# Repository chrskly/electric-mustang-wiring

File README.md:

# Electric Mustang Wiring

This repo contains the circuits, software, and wiring diagrams for my project to
convert a 1965 Ford Mustang to a EV.

## bms - Battery Management System

Schematic, PCB, and software for the battery management system.

## 12v-front-pcb

Schematic and PCB for wiring that sits in the front of the car (engine bay).

* Ignition switch
* Drive inhibition (preventing driving off when charging)
* Coolant pump
* Inverter
* Contactors
* Shunt

## 12v-lighting

Schematic and PCB for wiring for all of the lighting.

* Headlights/highbeams
* Indicators
* Brake lights
* Interior lights

## 12v-rear-pcb

Schematic and PCB for wiring that sits in the rear of the car (boot).

* On-board AC charger
* DC charger
* Charger VCU

## dashboard-vcu

Schematic and PCB for VCU to control the car dashboard.

## dashboard-vcu-src

Source code of dashboard vcu firmware.

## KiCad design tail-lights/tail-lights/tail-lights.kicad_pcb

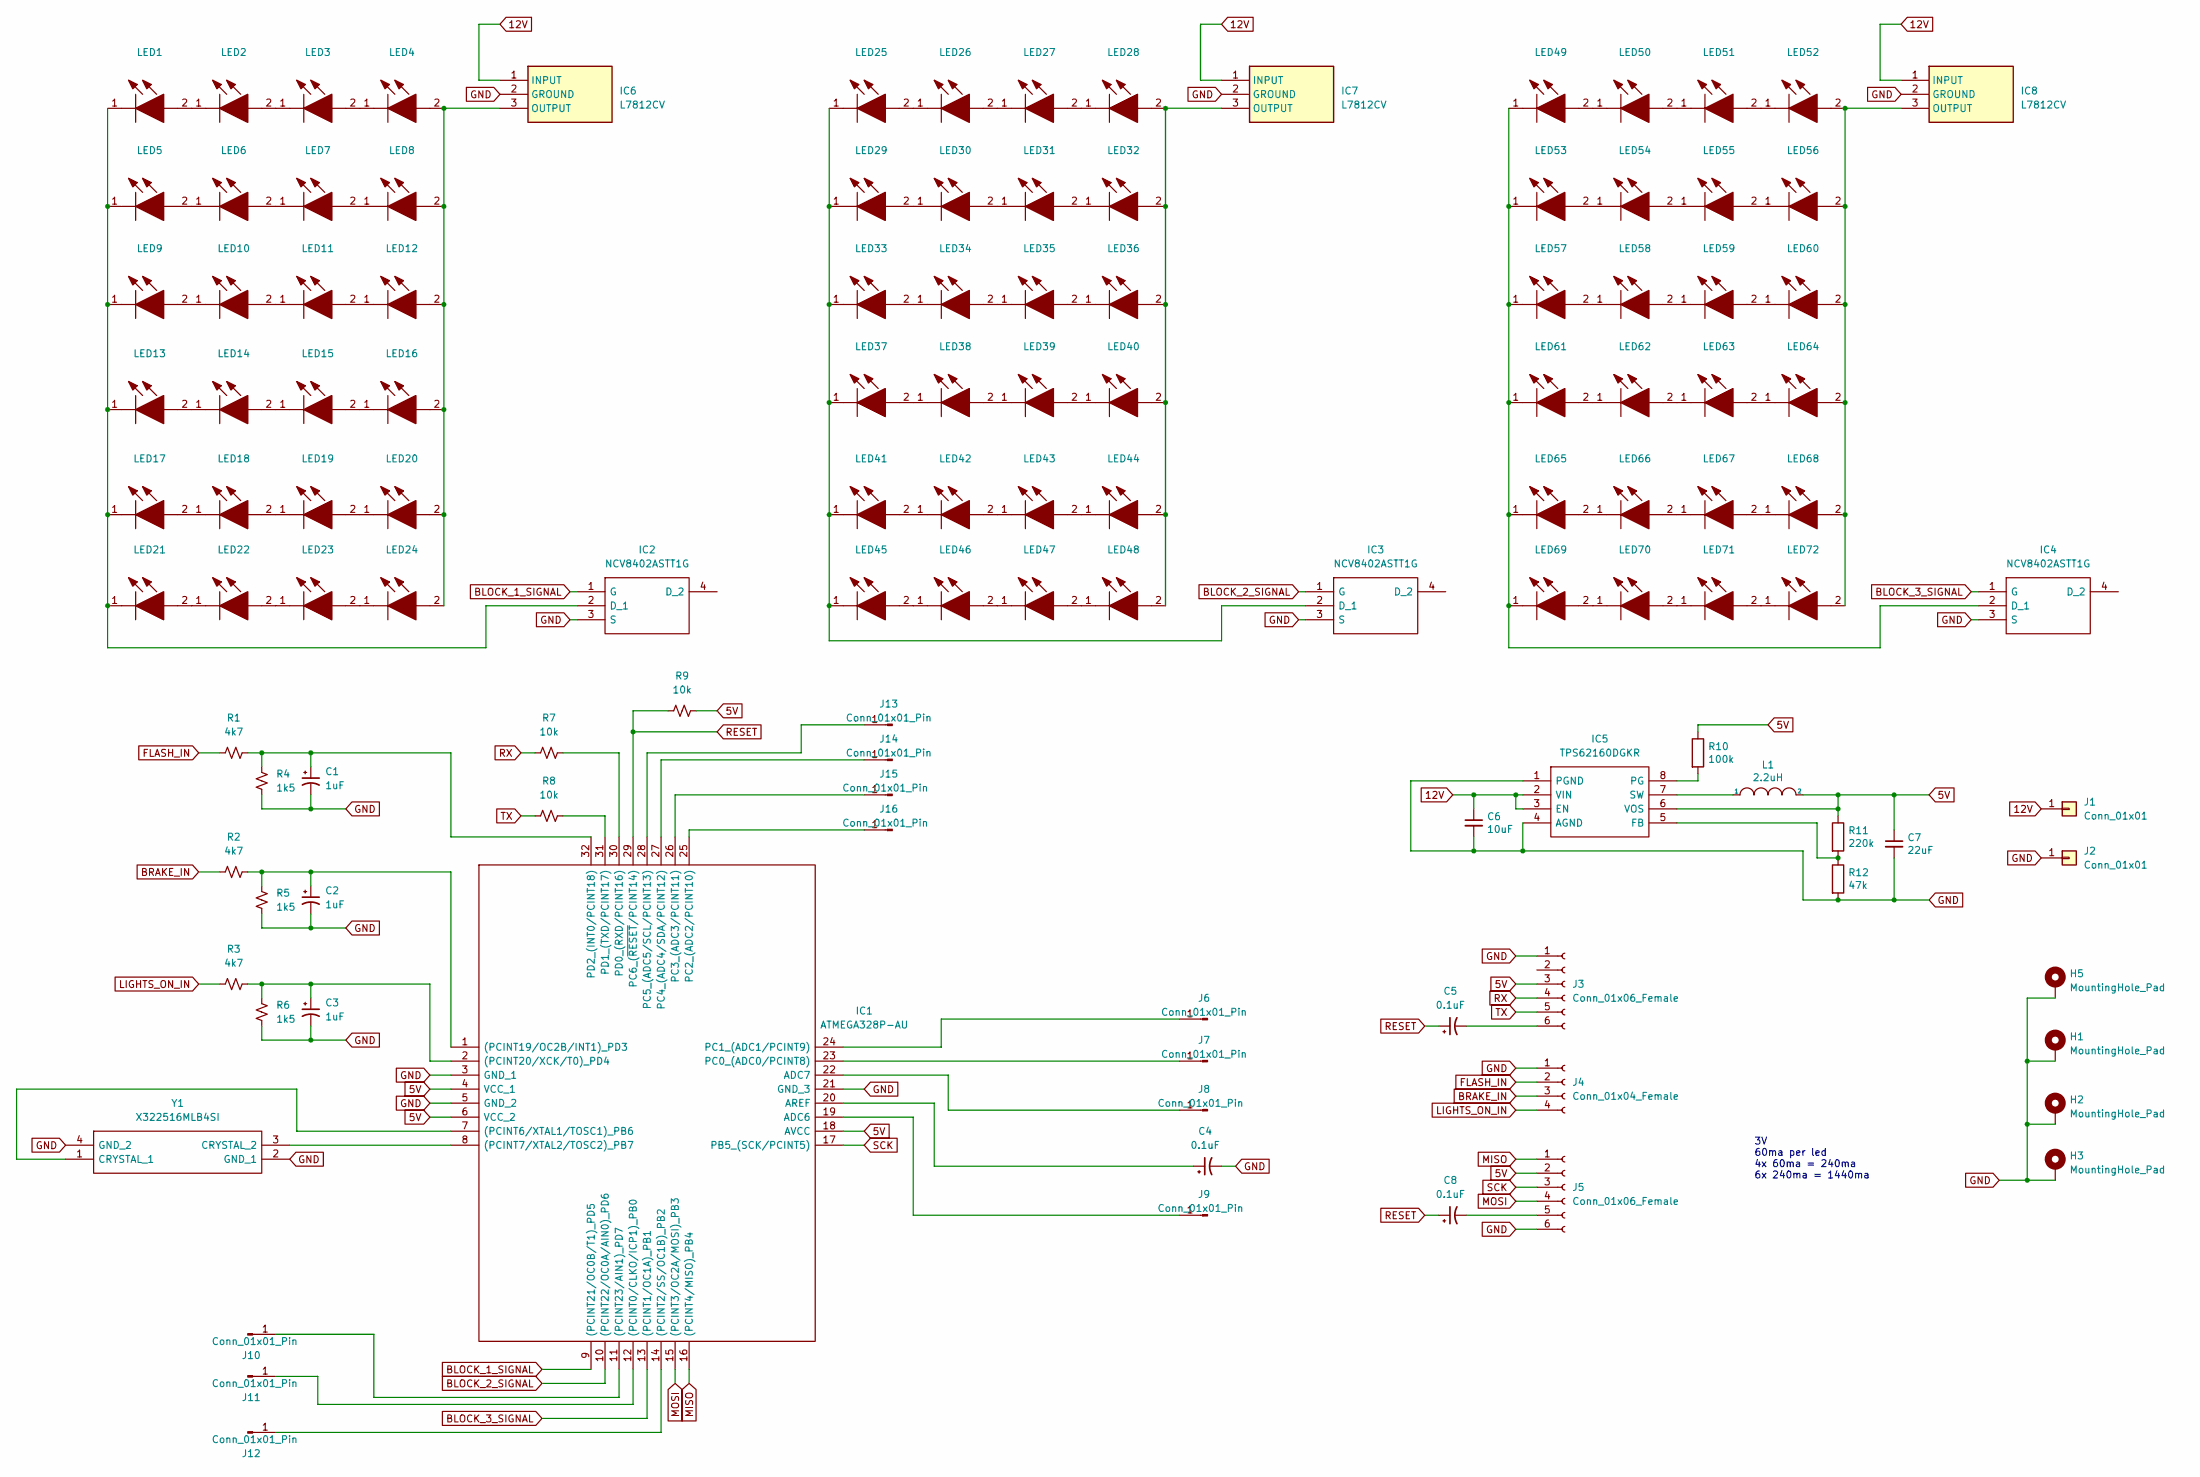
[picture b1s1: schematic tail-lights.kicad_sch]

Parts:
C1, C2, C3: 1uF; C_0603_1608Metric
C4, C5, C8: 0.1uF; C_0603_1608Metric
C6: 10uF; C_0603_1608Metric
C7: 22uF; C_0805_2012Metric
H1, H2, H3, H5: MountingHole_Pad; MountingHole_2.5mm_Pad
IC1: ATMEGA328P-AU; QFP80P900X900X120-32N; Manufacturer_Part_Number ATMEGA328P-AU; Mouser Part Number 556-ATMEGA328P-AU
IC2, IC3, IC4: NCV8402ASTT1G; SOT230P700X175-4N; Manufacturer_Part_Number NCV8402ASTT1G; Mouser Part Number 863-NCV8402ASTT1G
IC5: TPS62160DGKR; SOP65P490X110-8N; Manufacturer_Part_Number TPS62160DGKR; Mouser Part Number 595-TPS62160DGKR
IC6, IC7, IC8: L7812CV; TO255P460X1020X2008-3P; Manufacturer_Part_Number L7812CV; Mouser Part Number 511-L7812CV
J1, J2: Conn_01x01; SolderWire-1sqmm_1x01_D1.4mm_OD2.7mm
J3, J5: Conn_01x06_Female; PinHeader_1x06_P2.54mm_Vertical
J4: Conn_01x04_Female; PinHeader_1x04_P2.54mm_Vertical
J6, J7, J8, J9, J10, J11, J12, J13, J14, J15, J16: Conn_01x01_Pin; PinHeader_1x01_P2.54mm_Vertical
L1: 2.2uH; NR6028T220M
LED1, LED2, LED3, LED4, LED5, LED6, LED7, LED8, LED9, LED10, LED11, LED12, LED13, LED14, LED15, LED16, LED17, LED18, LED19, LED20, LED21, LED22, LED23, LED24, LED25, LED26, LED27, LED28, LED29, LED30, LED31, LED32, LED33, LED34, LED35, LED36, LED37, LED38, LED39, LED40, LED41, LED42, LED43, LED44, LED45, LED46, LED47, LED48, LED49, LED50, LED51, LED52, LED53, LED54, LED55, LED56, LED57, LED58, LED59, LED60, LED61, LED62, LED63, LED64, LED65, LED66, LED67, LED68, LED69, LED70, LED71, LED72: HL-AM-2835H421W-S1-08-HR3; HLAM2835H421WS108HR3; Manufacturer_Part_Number HL-AM-2835H421W-S1-08-HR3
R1, R2, R3: 4k7; R_0805_2012Metric
R4, R5, R6: 1k5; R_0805_2012Metric
R7, R8, R9: 10k; R_0805_2012Metric
R10: 100k; R_0805_2012Metric
R11: 220k; R_0805_2012Metric
R12: 47k; R_0805_2012Metric
Y1: X322516MLB4SI; Manufacturer_Part_Number X322516MLB4SI

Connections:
5V: C7.1, IC1.4 (VCC_1), IC1.6 (VCC_2), IC1.18 (AVCC), IC5.6 (VOS), J3.3, J5.2, L1.2, R9.2, R10.1, R11.1
12V: C6.1, IC5.2 (VIN), IC5.3 (EN), IC6.1 (INPUT), IC7.1 (INPUT), IC8.1 (INPUT), J1.1
BLOCK_1_SIGNAL: IC1.9 ((PCINT21/OC0B/T1)_PD5), IC2.1 (G)
BLOCK_2_SIGNAL: IC1.10 ((PCINT22/OC0A/AIN0)_PD6), IC3.1 (G)
BLOCK_3_SIGNAL: IC1.13 ((PCINT1/OC1A)_PB1), IC4.1 (G)
BRAKE_IN: J4.3, R2.1
FLASH_IN: J4.2, R1.1
GND: C1.2, C2.2, C3.2, C4.2, C6.2, C7.2, H1.1, H2.1, H3.1, H5.1, IC1.3 (GND_1), IC1.5 (GND_2), IC1.21 (GND_3), IC2.3 (S), IC3.3 (S), IC4.3 (S), IC5.1 (PGND), IC5.4 (AGND), IC6.2 (GROUND), IC7.2 (GROUND), IC8.2 (GROUND), J2.1, J3.1, J4.1, J5.6, R4.2, R5.2, R6.2, R12.2, Y1.2 (GND_1), Y1.4 (GND_2)
LIGHTS_ON_IN: J4.4, R3.1
MISO: IC1.16 ((PCINT4/MISO)_PB4), J5.1
MOSI: IC1.15 ((PCINT3/OC2A/MOSI)_PB3), J5.4
unnamed: IC1.12 ((PCINT0/CLKO/ICP1)_PB0), J11.1
unnamed: IC1.14 ((PCINT2/SS/OC1B)_PB2), J12.1
unnamed: IC1.7 ((PCINT6/XTAL1/TOSC1)_PB6), Y1.1 (CRYSTAL_1)
unnamed: IC1.8 ((PCINT7/XTAL2/TOSC2)_PB7), Y1.3 (CRYSTAL_2)
unnamed: C2.1, IC1.1 ((PCINT19/OC2B/INT1)_PD3), R2.2, R5.1
unnamed: C3.1, IC1.2 ((PCINT20/XCK/T0)_PD4), R3.2, R6.1
unnamed: IC1.11 ((PCINT23/AIN1)_PD7), J10.1
unnamed: IC1.19 (ADC6), J9.1
unnamed: IC1.22 (ADC7), J8.1
unnamed: C4.1, IC1.20 (AREF)
unnamed: IC1.23 (PC0_(ADC0/PCINT8)), J7.1
unnamed: IC1.24 (PC1_(ADC1/PCINT9)), J6.1
unnamed: IC1.25 (PC2_(ADC2/PCINT10)), J16.1
unnamed: IC1.26 (PC3_(ADC3/PCINT11)), J15.1
unnamed: IC1.27 (PC4_(ADC4/SDA/PCINT12)), J14.1
unnamed: IC1.28 (PC5_(ADC5/SCL/PCINT13)), J13.1
unnamed: IC1.30 (PD0_(RXD/PCINT16)), R7.2
unnamed: IC1.31 (PD1_(TXD/PCINT17)), R8.2
unnamed: C1.1, IC1.32 (PD2_(INT0/PCINT18)), R1.2, R4.1
unnamed: IC2.2 (D_1), LED1.1, LED5.1, LED9.1, LED13.1, LED17.1, LED21.1
unnamed: IC3.2 (D_1), LED25.1, LED29.1, LED33.1, LED37.1, LED41.1, LED45.1
unnamed: IC4.2 (D_1), LED49.1, LED53.1, LED57.1, LED61.1, LED65.1, LED69.1
unnamed: IC5.5 (FB), R11.2, R12.1
unnamed: IC5.8 (PG), R10.2
unnamed: IC5.7 (SW), L1.1
unnamed: IC6.3 (OUTPUT), LED4.2, LED8.2, LED12.2, LED16.2, LED20.2, LED24.2
unnamed: IC7.3 (OUTPUT), LED28.2, LED32.2, LED36.2, LED40.2, LED44.2, LED48.2
unnamed: IC8.3 (OUTPUT), LED52.2, LED56.2, LED60.2, LED64.2, LED68.2, LED72.2
unnamed: C5.2, J3.6
unnamed: C8.2, J5.5
unnamed: LED1.2, LED2.1
unnamed: LED2.2, LED3.1
unnamed: LED3.2, LED4.1
unnamed: LED5.2, LED6.1
unnamed: LED6.2, LED7.1
unnamed: LED7.2, LED8.1
unnamed: LED9.2, LED10.1
unnamed: LED10.2, LED11.1
unnamed: LED11.2, LED12.1
unnamed: LED13.2, LED14.1
unnamed: LED14.2, LED15.1
unnamed: LED15.2, LED16.1
unnamed: LED17.2, LED18.1
unnamed: LED18.2, LED19.1
unnamed: LED19.2, LED20.1
unnamed: LED21.2, LED22.1
unnamed: LED22.2, LED23.1
unnamed: LED23.2, LED24.1
unnamed: LED25.2, LED26.1
unnamed: LED26.2, LED27.1
unnamed: LED27.2, LED28.1
unnamed: LED29.2, LED30.1
unnamed: LED30.2, LED31.1
unnamed: LED31.2, LED32.1
unnamed: LED33.2, LED34.1
unnamed: LED34.2, LED35.1
unnamed: LED35.2, LED36.1
unnamed: LED37.2, LED38.1
unnamed: LED38.2, LED39.1
unnamed: LED39.2, LED40.1
unnamed: LED41.2, LED42.1
unnamed: LED42.2, LED43.1
unnamed: LED43.2, LED44.1
unnamed: LED45.2, LED46.1
unnamed: LED46.2, LED47.1
unnamed: LED47.2, LED48.1
unnamed: LED49.2, LED50.1
unnamed: LED50.2, LED51.1
unnamed: LED51.2, LED52.1
unnamed: LED53.2, LED54.1
unnamed: LED54.2, LED55.1
unnamed: LED55.2, LED56.1
unnamed: LED57.2, LED58.1
unnamed: LED58.2, LED59.1
unnamed: LED59.2, LED60.1
unnamed: LED61.2, LED62.1
unnamed: LED62.2, LED63.1
unnamed: LED63.2, LED64.1
unnamed: LED65.2, LED66.1
unnamed: LED66.2, LED67.1
unnamed: LED67.2, LED68.1
unnamed: LED69.2, LED70.1
unnamed: LED70.2, LED71.1
unnamed: LED71.2, LED72.1
RESET: C5.1, C8.1, IC1.29 (PC6_(~RESET/PCINT14)), R9.1
RX: J3.4, R7.1
SCK: IC1.17 (PB5_(SCK/PCINT5)), J5.3
TX: J3.5, R8.1

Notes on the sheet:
3V 60ma per led 4x 60ma = 240ma 6x 240ma = 1440ma

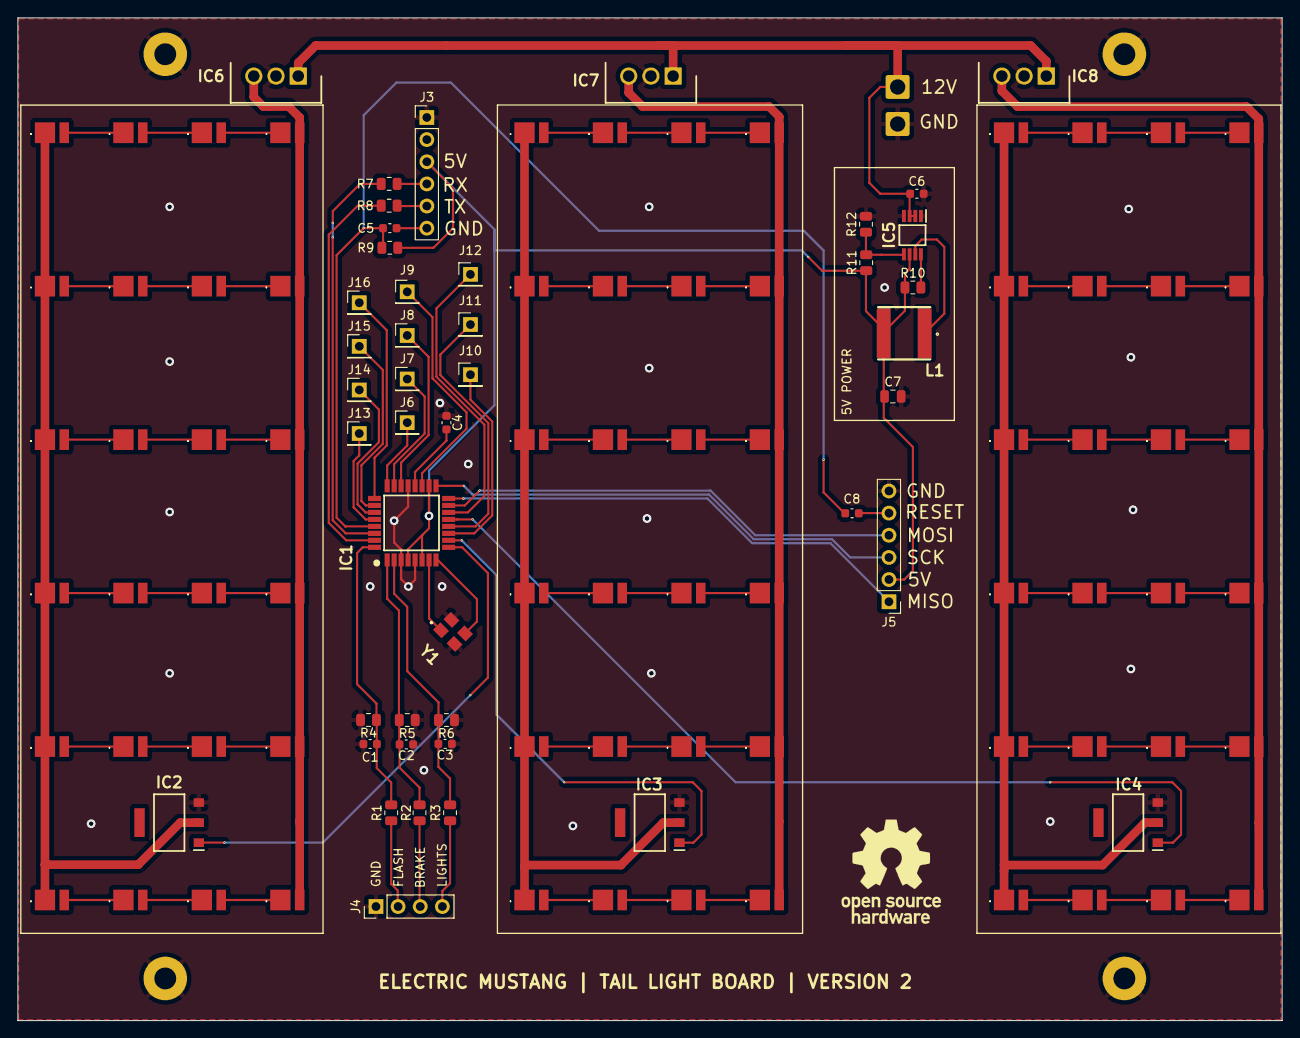
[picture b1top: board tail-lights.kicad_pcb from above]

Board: 2 copper layers, 145.0 x 115.0 mm, 122 parts (0 on the bottom side), 99 nets.

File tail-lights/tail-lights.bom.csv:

Comment,Designator,Footprint,LCSC
HL-AM-2835H421W-S1-08-HR3,"LED1,LED2,LED3,LED4,LED5,LED6,LED7,LED8,LED9,LED10,LED11,LED12,LED13,LED14,LED15,LED16,LED17,LED18,LED19,LED20,LED21,LED22,LED23,LED24,LED25,LED26,LED27,LED28,LED29,LED30,LED31,LED32,LED33,LED34,LED35,LED36,LED37,LED38,LED39,LED40,LED41,LED42,LED43,LED44,LED45,LED46,LED47,LED48,LED49,LED50,LED51,LED52,LED53,LED54,LED55,LED56,LED57,LED58,LED59,LED60,LED61,LED62,LED63,LED64,LED65,LED66,LED67,LED68,LED69,LED70,LED71,LED72",SMD2835,C210318
NCV8402ASTT1G,"IC2,IC3,IC4",SOT223,C77755
ATMEGA328P-AU,IC1,TQFP-32,C14877
4k7Ω,"R1,R2,R3",0805_R,C17673
1k5Ω,"R4,R5,R6",0805_R,C4310
1uF,"C1,C2,C3",0805_C,C28323
X322516MLB4SI,Y1,SMD3225-4P,C13738
10kΩ,"R7,R8,R9",0805_R,C84376
0.1uF,"C4,C5",0805_C,C49678
TPS62160DGKR,IC5,MSOP-8,C60726
10uF,C6,0805_C,C15850
100kΩ,R10,0805_R,C149504
2.2uH,L1,SMD,C135262
220kΩ,R11,0805_R,C17539
47kΩ,R12,0805_R,C17713
22uF,C7,0805_C,C2835558

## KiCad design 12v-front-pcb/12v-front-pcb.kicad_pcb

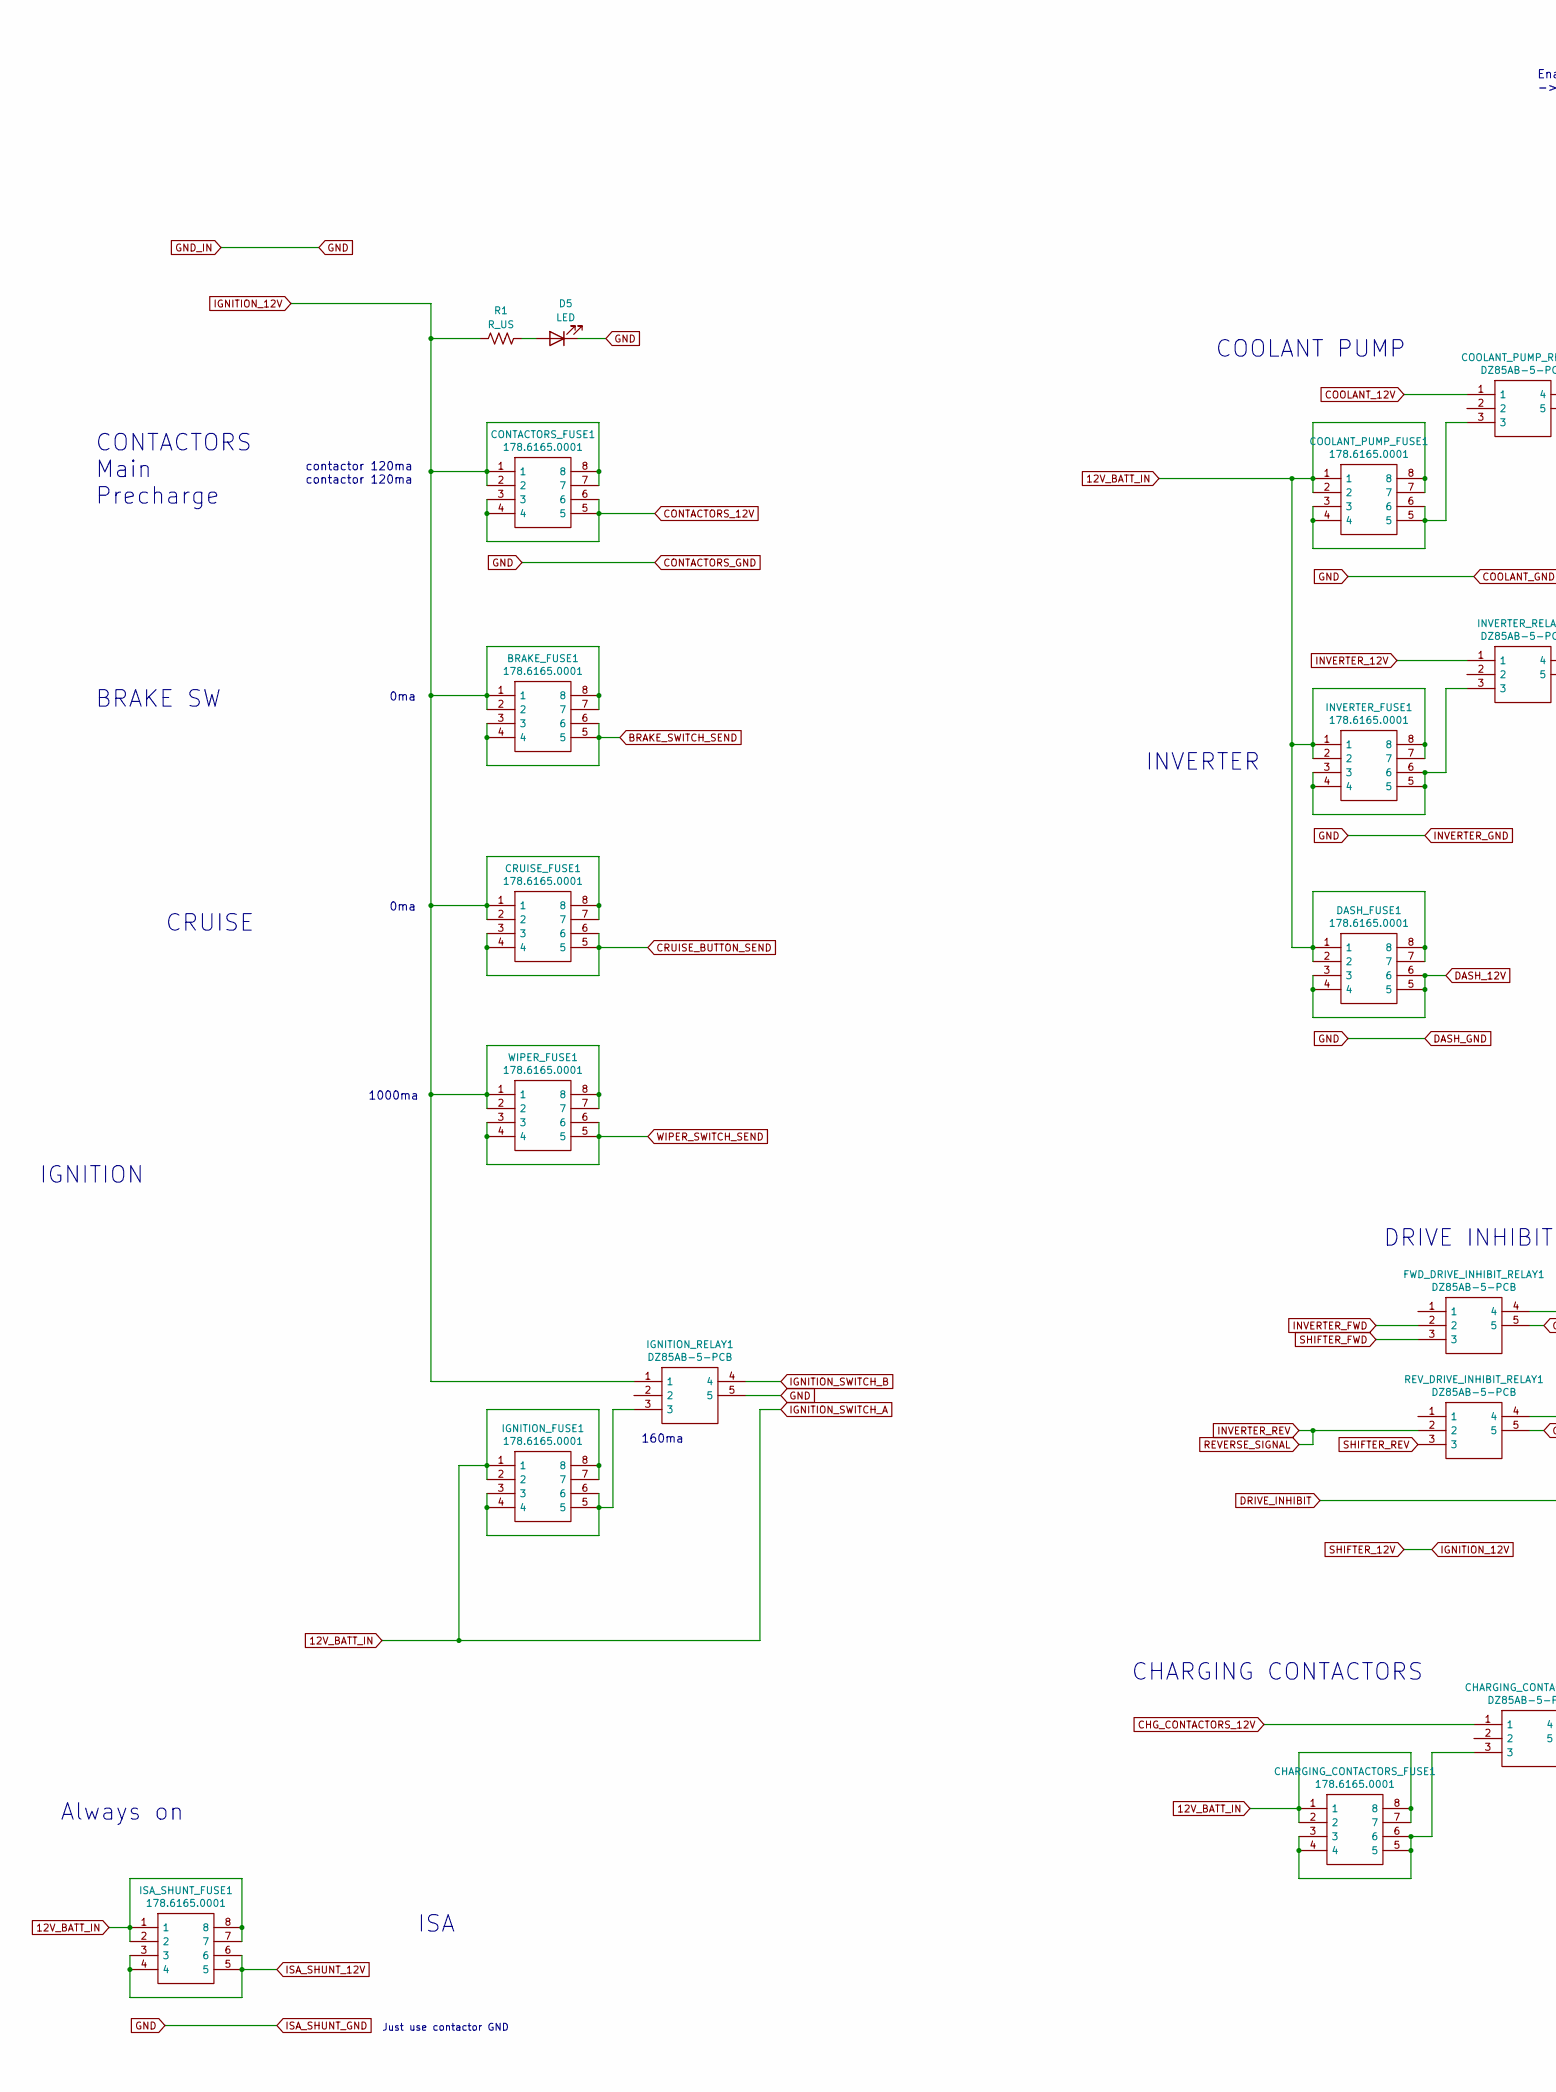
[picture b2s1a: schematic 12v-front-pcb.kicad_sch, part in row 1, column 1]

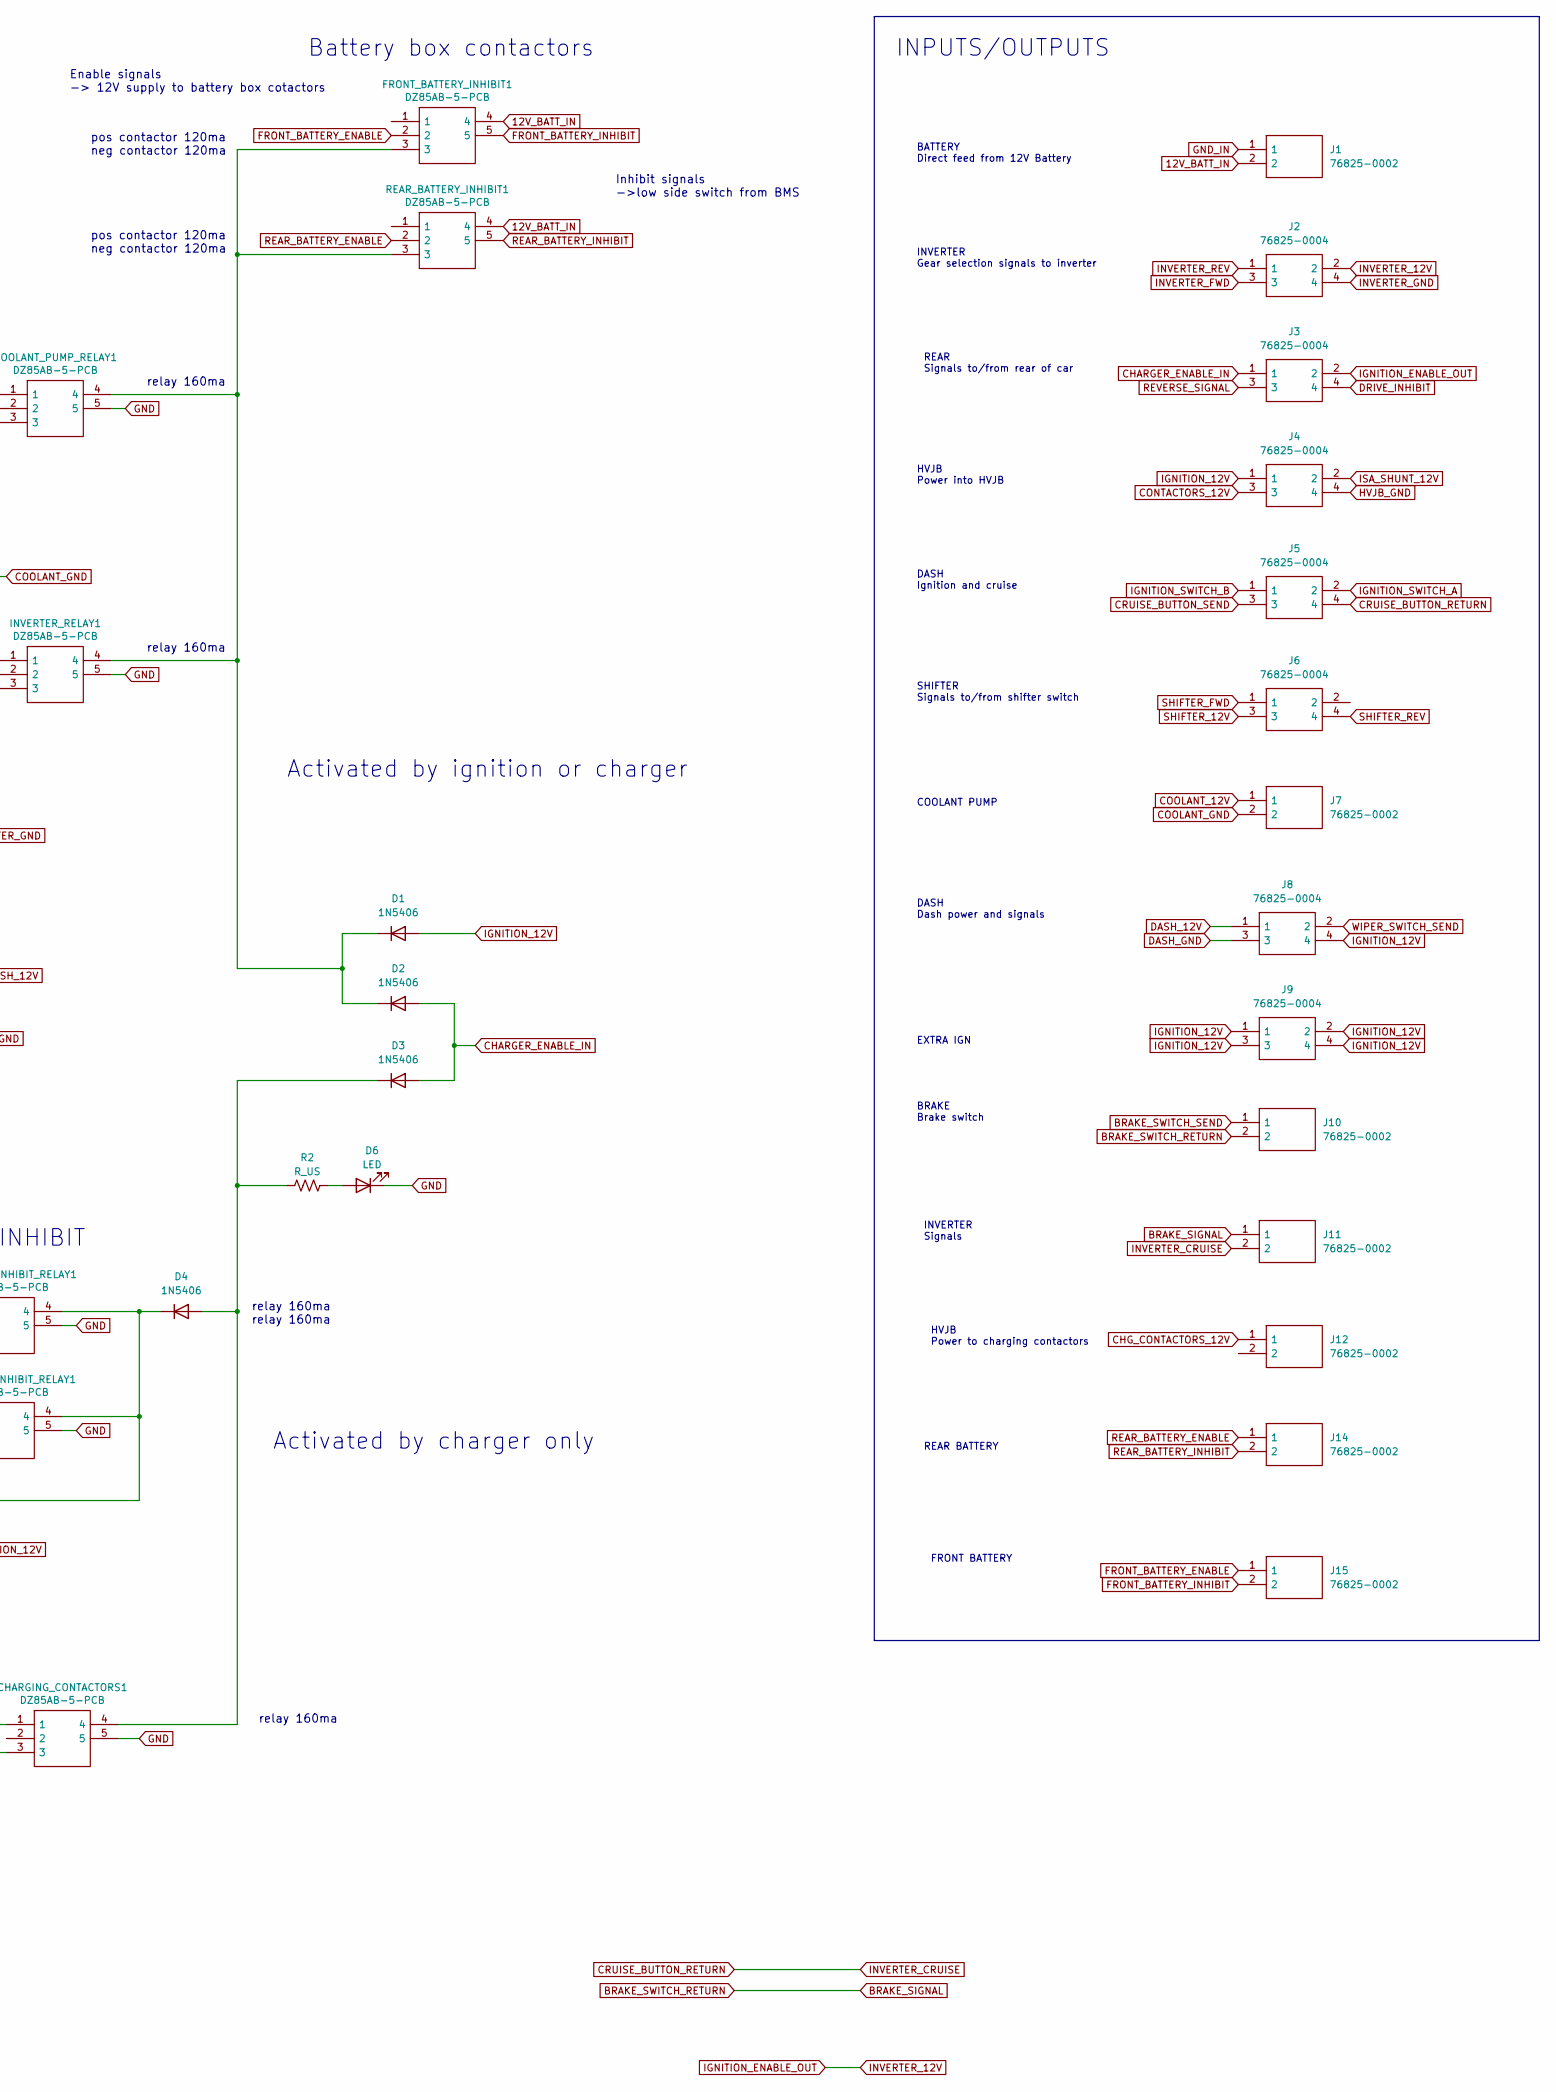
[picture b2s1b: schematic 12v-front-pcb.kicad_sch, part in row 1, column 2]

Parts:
BRAKE_FUSE1: 178.6165.0001; 17861650001; Manufacturer_Part_Number 178.6165.0001; Mouser Part Number 576-178.6165.0001
CHARGING_CONTACTORS1: DZ85AB-5-PCB; DZ85AB5PCB; Manufacturer_Part_Number DZ85AB-5-PCB
CHARGING_CONTACTORS_FUSE1: 178.6165.0001; 17861650001; Manufacturer_Part_Number 178.6165.0001; Mouser Part Number 576-178.6165.0001
CONTACTORS_FUSE1: 178.6165.0001; 17861650001; Manufacturer_Part_Number 178.6165.0001; Mouser Part Number 576-178.6165.0001
COOLANT_PUMP_FUSE1: 178.6165.0001; 17861650001; Manufacturer_Part_Number 178.6165.0001; Mouser Part Number 576-178.6165.0001
COOLANT_PUMP_RELAY1: DZ85AB-5-PCB; DZ85AB5PCB; Manufacturer_Part_Number DZ85AB-5-PCB
CRUISE_FUSE1: 178.6165.0001; 17861650001; Manufacturer_Part_Number 178.6165.0001; Mouser Part Number 576-178.6165.0001
D1, D2, D3, D4: 1N5406; D_DO-201AD_P15.24mm_Horizontal
D5, D6: LED; LED_D3.0mm_Clear
DASH_FUSE1: 178.6165.0001; 17861650001; Manufacturer_Part_Number 178.6165.0001; Mouser Part Number 576-178.6165.0001
FRONT_BATTERY_INHIBIT1: DZ85AB-5-PCB; DZ85AB5PCB; Manufacturer_Part_Number DZ85AB-5-PCB
FWD_DRIVE_INHIBIT_RELAY1: DZ85AB-5-PCB; DZ85AB5PCB; Manufacturer_Part_Number DZ85AB-5-PCB
IGNITION_FUSE1: 178.6165.0001; 17861650001; Manufacturer_Part_Number 178.6165.0001; Mouser Part Number 576-178.6165.0001
IGNITION_RELAY1: DZ85AB-5-PCB; DZ85AB5PCB; Manufacturer_Part_Number DZ85AB-5-PCB
INVERTER_FUSE1: 178.6165.0001; 17861650001; Manufacturer_Part_Number 178.6165.0001; Mouser Part Number 576-178.6165.0001
INVERTER_RELAY1: DZ85AB-5-PCB; DZ85AB5PCB; Manufacturer_Part_Number DZ85AB-5-PCB
ISA_SHUNT_FUSE1: 178.6165.0001; 17861650001; Manufacturer_Part_Number 178.6165.0001; Mouser Part Number 576-178.6165.0001
J1, J7, J10, J11, J12, J14, J15: 76825-0002; 768250002; Manufacturer_Part_Number 76825-0002; Mouser Part Number 538-76825-0002
J2, J3, J4, J5, J6, J8, J9: 76825-0004; 768250004; Manufacturer_Part_Number 76825-0004; Mouser Part Number 538-76825-0004
R1, R2: R_US; D_T-1_P2.54mm_Vertical_AnodeUp
REAR_BATTERY_INHIBIT1: DZ85AB-5-PCB; DZ85AB5PCB; Manufacturer_Part_Number DZ85AB-5-PCB
REV_DRIVE_INHIBIT_RELAY1: DZ85AB-5-PCB; DZ85AB5PCB; Manufacturer_Part_Number DZ85AB-5-PCB
WIPER_FUSE1: 178.6165.0001; 17861650001; Manufacturer_Part_Number 178.6165.0001; Mouser Part Number 576-178.6165.0001

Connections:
12V_BATT_IN: CHARGING_CONTACTORS_FUSE1.1, CHARGING_CONTACTORS_FUSE1.2, CHARGING_CONTACTORS_FUSE1.7, CHARGING_CONTACTORS_FUSE1.8, COOLANT_PUMP_FUSE1.1, COOLANT_PUMP_FUSE1.2, COOLANT_PUMP_FUSE1.7, COOLANT_PUMP_FUSE1.8, DASH_FUSE1.1, DASH_FUSE1.2, DASH_FUSE1.7, DASH_FUSE1.8, FRONT_BATTERY_INHIBIT1.4, IGNITION_FUSE1.1, IGNITION_FUSE1.2, IGNITION_FUSE1.7, IGNITION_FUSE1.8, INVERTER_FUSE1.1, INVERTER_FUSE1.2, INVERTER_FUSE1.7, INVERTER_FUSE1.8, ISA_SHUNT_FUSE1.1, ISA_SHUNT_FUSE1.2, ISA_SHUNT_FUSE1.7, ISA_SHUNT_FUSE1.8, J1.2, J5.2, REAR_BATTERY_INHIBIT1.4
BRAKE_SIGNAL: J10.2, J11.1
BRAKE_SWITCH_SEND: BRAKE_FUSE1.3, BRAKE_FUSE1.4, BRAKE_FUSE1.5, BRAKE_FUSE1.6, J10.1
CHARGER_ENABLE_IN: D2.2 (A), D3.2 (A), J3.1
CHG_CONTACTORS_12V: CHARGING_CONTACTORS1.1, J12.1
CONTACTORS_12V: CONTACTORS_FUSE1.3, CONTACTORS_FUSE1.4, CONTACTORS_FUSE1.5, CONTACTORS_FUSE1.6, J4.3
CONTACTORS_GND: CHARGING_CONTACTORS1.5, COOLANT_PUMP_RELAY1.5, D5.1 (K), D6.1 (K), FWD_DRIVE_INHIBIT_RELAY1.5, IGNITION_RELAY1.5, INVERTER_RELAY1.5, J1.1, J2.4, J7.2, J8.3, REV_DRIVE_INHIBIT_RELAY1.5
COOLANT_12V: COOLANT_PUMP_RELAY1.1, J7.1
CRUISE_BUTTON_RETURN: J5.4, J11.2
CRUISE_BUTTON_SEND: CRUISE_FUSE1.3, CRUISE_FUSE1.4, CRUISE_FUSE1.5, CRUISE_FUSE1.6, J5.3
DASH_12V: DASH_FUSE1.3, DASH_FUSE1.4, DASH_FUSE1.5, DASH_FUSE1.6, J8.1
DRIVE_INHIBIT: D4.1 (K), FWD_DRIVE_INHIBIT_RELAY1.4, J3.4, REV_DRIVE_INHIBIT_RELAY1.4
FRONT_BATTERY_ENABLE: FRONT_BATTERY_INHIBIT1.2, J15.1
FRONT_BATTERY_INHIBIT: FRONT_BATTERY_INHIBIT1.5, J15.2
HVJB_GND: J4.4
IGNITION_12V: BRAKE_FUSE1.1, BRAKE_FUSE1.2, BRAKE_FUSE1.7, BRAKE_FUSE1.8, CONTACTORS_FUSE1.1, CONTACTORS_FUSE1.2, CONTACTORS_FUSE1.7, CONTACTORS_FUSE1.8, CRUISE_FUSE1.1, CRUISE_FUSE1.2, CRUISE_FUSE1.7, CRUISE_FUSE1.8, D1.2 (A), IGNITION_RELAY1.1, J4.1, J6.3, J8.4, J9.1, J9.2, J9.3, J9.4, R1.1, WIPER_FUSE1.1, WIPER_FUSE1.2, WIPER_FUSE1.7, WIPER_FUSE1.8
IGNITION_ENABLE_OUT: INVERTER_RELAY1.1, J2.2, J3.2
IGNITION_SWITCH_B: IGNITION_RELAY1.4, J5.1
INVERTER_FWD: FWD_DRIVE_INHIBIT_RELAY1.2, J2.3
INVERTER_REV: J2.1, J3.3, REV_DRIVE_INHIBIT_RELAY1.2
ISA_SHUNT_12V: ISA_SHUNT_FUSE1.3, ISA_SHUNT_FUSE1.4, ISA_SHUNT_FUSE1.5, ISA_SHUNT_FUSE1.6, J4.2
unnamed: CHARGING_CONTACTORS1.3, CHARGING_CONTACTORS_FUSE1.3, CHARGING_CONTACTORS_FUSE1.4, CHARGING_CONTACTORS_FUSE1.5, CHARGING_CONTACTORS_FUSE1.6
unnamed: COOLANT_PUMP_FUSE1.3, COOLANT_PUMP_FUSE1.4, COOLANT_PUMP_FUSE1.5, COOLANT_PUMP_FUSE1.6, COOLANT_PUMP_RELAY1.3
unnamed: COOLANT_PUMP_RELAY1.4, D1.1 (K), D2.1 (K), FRONT_BATTERY_INHIBIT1.3, INVERTER_RELAY1.4, REAR_BATTERY_INHIBIT1.3
unnamed: CHARGING_CONTACTORS1.4, D3.1 (K), D4.2 (A), R2.1
unnamed: D5.2 (A), R1.2
unnamed: D6.2 (A), R2.2
unnamed: IGNITION_FUSE1.3, IGNITION_FUSE1.4, IGNITION_FUSE1.5, IGNITION_FUSE1.6, IGNITION_RELAY1.3
unnamed: INVERTER_FUSE1.3, INVERTER_FUSE1.4, INVERTER_FUSE1.5, INVERTER_FUSE1.6, INVERTER_RELAY1.3
REAR_BATTERY_ENABLE: J14.1, REAR_BATTERY_INHIBIT1.2
REAR_BATTERY_INHIBIT: J14.2, REAR_BATTERY_INHIBIT1.5
SHIFTER_FWD: FWD_DRIVE_INHIBIT_RELAY1.3, J6.1
SHIFTER_REV: J6.4, REV_DRIVE_INHIBIT_RELAY1.3
WIPER_SWITCH_SEND: J8.2, WIPER_FUSE1.3, WIPER_FUSE1.4, WIPER_FUSE1.5, WIPER_FUSE1.6

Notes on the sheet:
INVERTER Gear selection signals to inverter
HVJB Power to charging contactors
IGNITION
Inhibit signals ->low side switch from BMS
BRAKE SW
BATTERY Direct feed from 12V Battery
relay 160ma relay 160ma
HVJB Power into HVJB
COOLANT PUMP
relay 160ma
BRAKE Brake switch
SHIFTER Signals to/from shifter switch
Enable signals -> 12V supply to battery box cotactors
Always on
contactor 120ma contactor 120ma
FRONT BATTERY
INVERTER Signals
Activated by ignition or charger
EXTRA IGN
1000ma
INPUTS/OUTPUTS
ISA
Battery box contactors
CONTACTORS Main Precharge
INVERTER
pos contactor 120ma neg contactor 120ma
REAR Signals to/from rear of car
DASH Ignition and cruise
DASH Dash power and signals
Activated by charger only
CHARGING CONTACTORS
0ma
CRUISE
REAR BATTERY
Just use contactor GND
DRIVE INHIBIT
160ma

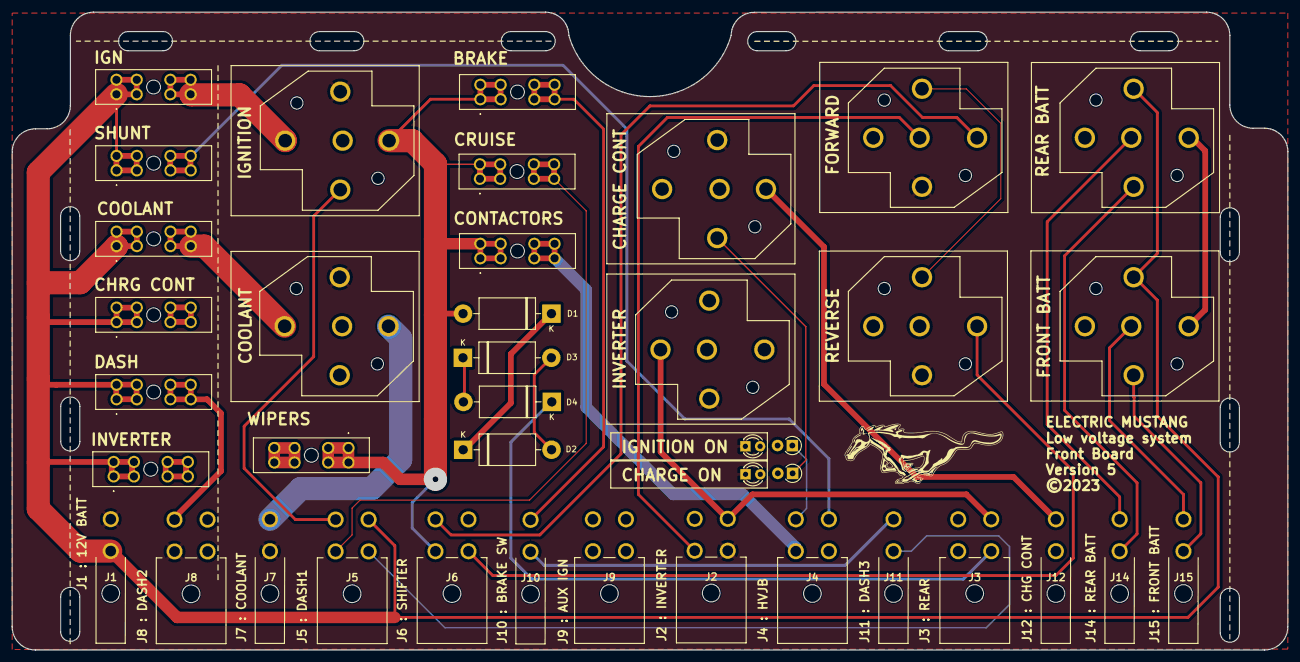
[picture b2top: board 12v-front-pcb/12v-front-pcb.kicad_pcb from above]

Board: 4 copper layers, 220.0 x 110.0 mm, 40 parts (0 on the bottom side), 33 nets.

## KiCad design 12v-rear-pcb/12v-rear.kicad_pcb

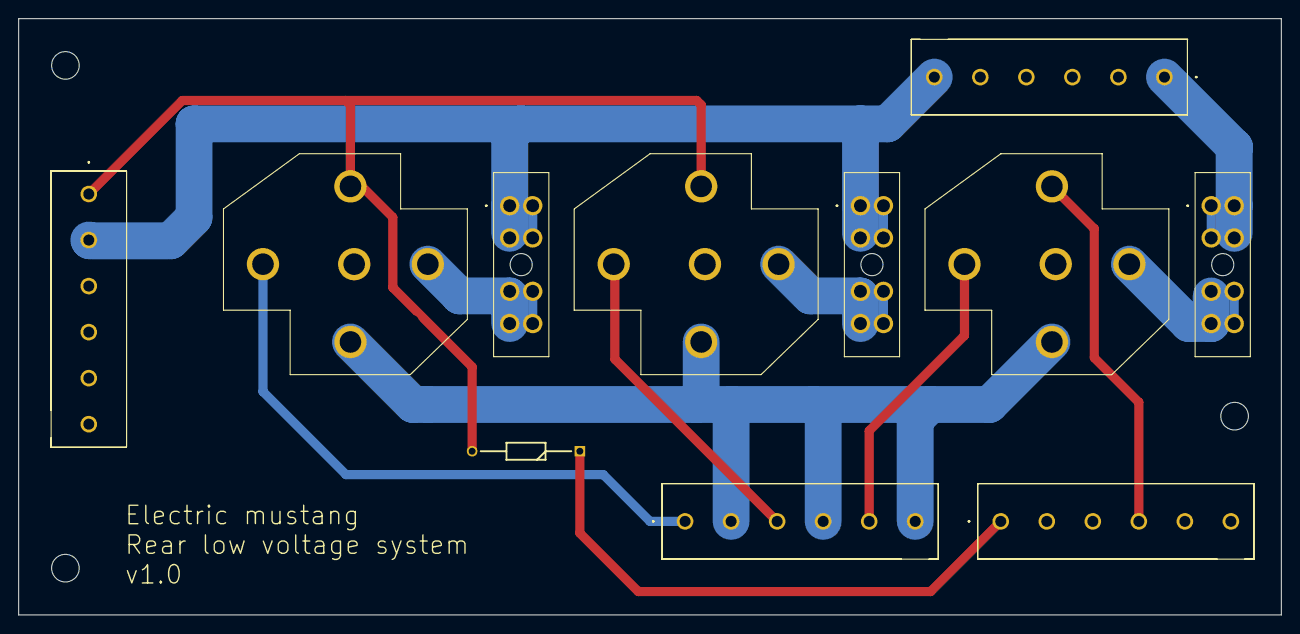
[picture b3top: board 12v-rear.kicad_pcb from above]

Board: 2 copper layers, 137.2 x 64.8 mm, 14 parts (0 on the bottom side), 12 nets.

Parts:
D1: 10A10; DIOAD1165W56L425D185
FRONT_1, FRONT_2: 282836-6; 2828366
H1, H2, H3: MountingHole; MountingHole_3mm
LIM_FUSE1: 178.6165.0001; 17861650001
LIM_RELAY1: DZ85AB-5-PCB; DZ85AB5PCB
REAR_1, REAR_2: 282836-6; 2828366
REVERSE_LIGHT_FUSE1: 178.6165.0001; 17861650001
REVERSE_LIGHT_RELAY1: DZ85AB-5-PCB; DZ85AB5PCB
TESLA_FUSE1: 178.6165.0001; 17861650001
TESLA_RELAY1: DZ85AB-5-PCB; DZ85AB5PCB

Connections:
CHARGER_ON_SIGNAL: D1.1, FRONT_2.1
CHARGER_SWITCH_A: FRONT_1.6, LIM_FUSE1.1, LIM_FUSE1.2, LIM_FUSE1.7, LIM_FUSE1.8, REAR_2.2, TESLA_FUSE1.1, TESLA_FUSE1.2, TESLA_FUSE1.7, TESLA_FUSE1.8
CHARGER_SWITCH_B: D1.2, LIM_RELAY1.5, REAR_2.1, TESLA_RELAY1.5
GND: LIM_RELAY1.4, REAR_1.2, REAR_1.4, REAR_1.6, REVERSE_LIGHT_RELAY1.4, TESLA_RELAY1.4
IGNITION_12V: FRONT_1.1, REVERSE_LIGHT_FUSE1.1, REVERSE_LIGHT_FUSE1.2, REVERSE_LIGHT_FUSE1.7, REVERSE_LIGHT_FUSE1.8
LIM_12V: LIM_RELAY1.3, REAR_1.3
unnamed: LIM_FUSE1.3, LIM_FUSE1.4, LIM_FUSE1.5, LIM_FUSE1.6, LIM_RELAY1.1
unnamed: REVERSE_LIGHT_FUSE1.3, REVERSE_LIGHT_FUSE1.4, REVERSE_LIGHT_FUSE1.5, REVERSE_LIGHT_FUSE1.6, REVERSE_LIGHT_RELAY1.1
unnamed: TESLA_FUSE1.3, TESLA_FUSE1.4, TESLA_FUSE1.5, TESLA_FUSE1.6, TESLA_RELAY1.1
REVERSE_LIGHT: REAR_1.5, REVERSE_LIGHT_RELAY1.3
REVERSE_SIGNAL: FRONT_2.4, REVERSE_LIGHT_RELAY1.5
TESLA_12V: REAR_1.1, TESLA_RELAY1.3

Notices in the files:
12v-front-pcb/12v-front-pcb.kicad_pcb:
©2023
bms/pcb/bms/bms.kicad_pcb:
© 2022
